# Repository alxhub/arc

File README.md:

# ARC — model railroad control

ARC is my hobby ecosystem of model railroad control systems. It is designed as an integrated, full stack system, from the computer running the layout to the boards powering track districts, moving turnouts, and lighting signal masts.

The design emphasizes global processing and specialized boards for dedicated tasks. A layout computer knows the track plan and coordinates the whole railroad, while distributed hardware provides the power, sensing, and local control each task needs. This gives the software a layout-wide view while keeping physical connections close to the equipment they serve.

ARC is designed for evolving and temporary layouts, with plug-and-play operation as a guiding goal. Common capabilities are available throughout the system, so changing the track plan can be an ordinary part of using the railroad. That flexibility goes hand in hand with intelligent control: the computer can use its knowledge of track connections and turnout positions to prepare the hardware for a route.

This repository contains ARC's schematics written in [Stackup](https://github.com/stackup-eda/stackup) and the corresponding KiCad PCB projects. Stackup is another of my projects: a declarative language and toolchain for describing electronic circuits as text. It expresses parts, reusable circuits, connections, and design constraints, checks them together, and exports the result for KiCad. Stackup uses KDL as its file syntax, which is why the schematic sources have a `.kdl` extension.

The architecture and intended system behavior are described below; individual board READMEs cover their roles and design decisions. [Control architecture](CONTROL.md) describes the administrative, operations, control, and field planes, including district policy and PSU authority on loss of communication. [ARC CAN protocol](PROTOCOL.md) defines the wire format and node identity scheme.

## Three levels of control

ARC organizes the layout into three levels:

1. **The layout computer**, usually a Raspberry Pi, knows the track plan, runs the layout, and coordinates its behavior. The ARC HAT connects the Pi to the backbone and provides control of the layout's master contactor.
2. **The ARC-Link backbone** connects primary functional boards, including DCC district drivers and Trackside Hubs, over CAN. These boards typically live together in one or more clusters around the layout and are DIN-rail mountable.
3. **Trackside bus legs** extend from those clusters along the rails. They connect boards that serve a local purpose, such as a signal mast, turnout, servo, or vehicle tag reader.

A **Trackside Hub is a backbone board** that connects these last two levels. It receives commands over ARC-Link and manages up to three separate trackside bus legs, using LIN for local signaling. This arrangement lets the backbone connect clusters of functional hardware while the trackside wiring follows the railroad to individual accessories.

## Power and installation

ARC is designed for industrial DC power supplies: **12 V for N scale** and **15 V for HO scale**, with a particular emphasis on DIN-rail mounted supplies. Primary backbone boards share that mounting approach, making it practical to assemble a cluster of power and control hardware together.

The power architecture distinguishes the supply carried by ARC-Link from the power delivered to the rails and accessories. The supply board switches power onto ARC-Link; district drivers and Trackside Hubs also have their own connections to the layout's supply for their loads. District drivers generate rail power locally from the shared DCC timing signal.

## ARC-Link: the backbone

ARC-Link carries power, CAN communication, and DCC synchronization over **eight-wire Ethernet cable**:

| Conductors | Purpose |
| --- | --- |
| 2 | Backbone power |
| 2 | Backbone ground |
| 2 | CAN differential pair for commands and status |
| 2 | DCC differential pair for synchronized track timing |

Ethernet cable is the wiring medium; ARC-Link uses CAN for communication. The separate DCC pair carries timing, not the traction current delivered to the rails. The supply board normally generates that timing, and district drivers use it to produce their individual DCC outputs.

**Ground loop isolation is a central design priority.** The supply board establishes the backbone's ground reference, and other active backbone boards isolate their local circuits from the link. This separates the backbone reference from local track supply returns and control wiring as the system extends between clusters around the layout.

ARC-Link is distinct from LCC. Support for LCC devices is planned through a dedicated **ARC ↔ LCC bridge**, allowing those devices to participate in the layout alongside ARC hardware.

## The trackside bus

The trackside bus uses **four-wire telephone cable with RJ-11 connectors**. Each leg carries four connections:

| Conductor | Purpose |
| --- | --- |
| Track voltage | The layout's track-voltage supply for local loads |
| 5 V | Low-voltage power |
| Ground | Local power and signaling return |
| LIN | Commands and status for trackside boards |

These legs typically parallel the rails, keeping accessory wiring near the devices it serves. A signal controller can sit near its mast, a turnout controller near its turnout machines, and a tag reader near its separate antenna flex.

Each Trackside Hub manages up to three legs and can switch them independently. Its backbone connection crosses an isolation boundary; the trackside legs share the hub's local power and return.

## A dedicated output for every district

ARC calls a track block a **district** and standardizes on a distinct, independently controlled power feed for each one. The system is optimized for many separate outputs, with district boards providing four, six, or eight outputs per board. This makes each district a unit of power control, sensing, and fault handling.

Every district is designed to include the same core capabilities:

- **Built-in block detection through drive-current sensing.** This detects locomotives, but does not detect resistive wheelsets.
- **Built-in autoreversing.** Each district can reverse its output phase as needed for reversing track arrangements, including advance changes coordinated by the layout computer.
- **Programming-track operation on demand.** Any district can serve as a fully featured programming track when needed, with a separate programming signal and a lower current limit.
- **Independent control and fault reporting.** Each output can be switched and monitored separately, so a fault can be identified and handled at the affected district.

These capabilities are part of the district design rather than separate accessories to add to selected sections. A district's role can change with the layout's needs, including switching between normal running and programming operation.

## Layouts that evolve, control that understands them

Having autoreversing available in every district makes it easier to experiment with the track plan. Add a reversing loop on a whim, and the surrounding districts already have the phase control they need: there is no need to carefully rewire them around a specially designated reversing output. Dedicated district feeds and a controller that knows the revised track plan provide the basis for this plug-and-play approach.

That global picture also enables proactive polarity control. ARC is designed to use the track plan and turnout configurations to align district polarities automatically before wheels cross a boundary and cause a short. The layout computer can coordinate the outputs involved in a route because it knows how those sections connect.

The Kato turntable controller is another example of this intended behavior. As the turntable spins, ARC can use its knowledge of the table's position and connecting tracks to align their polarities automatically. The specialized board operates the turntable, while the layout-wide picture makes coordinated track power possible.

## Backbone boards

| Board | Role |
| --- | --- |
| [ARC-PSU-01](backbone/psu-01/README.md) | Switches power onto ARC-Link and normally generates DCC timing. |
| [ARC-HAT-01](backbone/hat-01/README.md) | Connects a Raspberry Pi to CAN and controls the layout contactor. |
| [ARC-EX-ARC](backbone/ex-arc/README.md) | Connects a CommandStation-EX and its motor shield to ARC. |
| [ARC-TERM-01](backbone/term-01/README.md) | Terminates the CAN and DCC pairs at the end of a run. |
| [ARC-DST-01x4 rev 2](backbone/dst-01x4/README.md) | Drives four independent track districts. |
| [ARC-DST-01x6](backbone/dst-01x6/README.md) | Drives six independent track districts. |
| [ARC-DST-01x8](backbone/dst-01x8/README.md) | Drives eight independent track districts. |
| [ARC-YRD-01x8](backbone/yrd-01x8/README.md) | Controls yard turnouts and signal lamps. |
| [ARC-TRK-HUB-01](backbone/trk-hub-01/README.md) | Bridges backbone CAN to three trackside LIN runs. |

## Trackside boards

| Board | Role |
| --- | --- |
| [ARC-TRK-LED-01](trackside/trk-led-01/README.md) | Drives signal lamps on a LIN run. |
| [ARC-TRK-SRV-01](trackside/trk-srv-01/README.md) | Drives servos, sound, and a signal head. |
| [ARC-TRK-NFC-01](trackside/trk-nfc-01/README.md) | Reads vehicle tags with a separate antenna. |
| [ARC-TRK-ANT-01](trackside/trk-ant-01/README.md) | Provides the reader's flexible track antenna. |
| [ARC-TRK-TRN-01](trackside/trk-trn-01/README.md) | Operates four turnout machines. |
| [ARC-TRK-TBL-01xK](trackside/trk-tbl-01xK/README.md) | Operates a Kato turntable. |

## Firmware

The [Rust firmware workspace](firmware/README.md) uses Embassy. It contains the
shared ARC-Link protocol crate at `firmware/shared/link`, the shared DCC packet
and waveform generator at `firmware/shared/dcc`, the `dst-01` board
crate for x4 rev1/rev2, and the `psu-01` board crate for link power, a
bounded locomotive table, and DCC idle and speed packets. DST rev1 includes the
same transmitter, disabled at boot. PSU and DST rev1 both require
[CAN transmit permission](PROTOCOL.md#dcc-control-message-0x01-grant), retained until
the source restarts. Once the expected layout is good, layoutd selects one master
and grants permission. PSU link power and CAN discovery start independently of DCC.
All current firmware targets also use an Embassy bootloader and a shared
[CAN FD update protocol](PROTOCOL.md#firmware-update-over-can-fd) for staged
application updates.

## Layout software

The first host-side service is [layoutd](services/layoutd/README.md). It owns
retained MQTT facts about track nodes, derives and checks the layout graph
against observed CAN node identities, and publishes overall status. Its CAN interface supports file snapshots and the virtual CAN bus for development
and tests. It selects the DCC master only after all expected hardware is accounted for.

The initial [dispatchd](services/dispatchd/README.md) bridge reads district
status and PSU throttle status from the virtual CAN bus, publishes MQTT state
under `/<layout>/district/` and `/<layout>/loco/`, and converts non-retained
locomotive commands to CAN throttle-set frames. PSU and DST rev1 share the
locomotive table and require the transmit grant assigned by layoutd.

The [virtual CAN lab](sim/README.md) builds the DST-01x4 firmware crate as host
binaries for both board revisions and connects them over a simulated CAN bus.
Its world clock starts paused; tests advance it explicitly so CAN arbitration,
PSU and district timers, DCC delivery, track motion, and current sampling share
the same time. The physical track fixture is separate from layoutd's configured
layout, allowing tests to exercise unknown or incorrect track plans.

## Working with the designs

The boards are composed from reusable Stackup circuits in [`shared/`](shared/). Each board directory keeps its `board.kdl`, supporting Stackup sources, functional README, and KiCad PCB project together.

The designs import the [Stackup parts library](https://github.com/stackup-eda/library), pinned in `manifest.kdl`. For local development, add a `manifest.local.kdl` with a path to a parts checkout:

```kdl
library stackup path="../stackup-parts"
```

Run `stackup check backbone/psu-01/board.kdl` to validate a board. Substitute any other board's `board.kdl` path as needed. Use `--locked` to check against the pinned library commit. Without a local override, the CLI fetches Git libraries into `.stackup/cache/` beside `manifest.kdl`.

Each KiCad PCB has a `.stackup_sch` sidecar pointing to the adjacent `board.kdl`. To sync a closed board with the Stackup KiCad plugin, using KiCad's bundled Python (`STACKUP_KDL` is the path to the Stackup worktree):

```sh
/Applications/KiCad/KiCad.app/Contents/Frameworks/Python.framework/Versions/3.9/bin/python3 \
  "$STACKUP_KDL/kicad-plugin/sync_headless.py" \
  backbone/term-01/term-01.kicad_pcb
```

The PCB layouts retain their routed copper and KiCad project settings. Some newer parts in the district and yard schematics still need placement and routing. A Stackup check or PCB sync is not a DRC or fabrication signoff. The antenna board retains an older footprint table as `fp-lib-table.legacy` for reference; KiCad uses its existing `fp-lib-table`.

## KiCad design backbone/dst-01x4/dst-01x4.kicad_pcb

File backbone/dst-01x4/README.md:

# ARC-DST-01x4 rev 2

ARC-DST-01x4 drives four track districts. It receives the shared DCC timing signal from the ARC backbone, then lets the controller set each district's phase and turn each output on or off independently. A district can also switch to a separate programming signal with a lower current limit.

The board has its own connection to the layout's track supply. It reports total track current and supply voltage to the controller, while each district reports its own current and fault state. That lets the system identify and respond to a problem in one section without treating all four sections as one output.

CAN connects the board to the rest of ARC for commands and status. The backbone's electrical isolation keeps its return separate from the track supply return. Board and district lights show status locally; a temperature sensor and fan support operation under load.

[Board design](board.kdl)
[PCB layout](dst-01x4.kicad_pcb)

## Firmware revisions

The Embassy firmware crate is [`firmware/dst-01`](../../firmware/dst-01), with
the `x4` variant feature and exactly one hardware revision feature:

| Feature | MCU | District control |
| --- | --- | --- |
| `rev1` | STM32G0B1RE | Two TCA9534 I/O expanders at `0x20` and `0x21`, on I²C3 (PC0 SCL / PC1 SDA) |
| `rev2` | STM32C092CB | Direct MCU GPIO, as described in the adjacent KDL sources |

Rev1's expanders carry phase, programming selection, sleep, and fault signals;
its PWM gates and analog sense inputs connect directly to the MCU. Rev1 is still
a firmware build target even though its Stackup design toolchain is retired.
Its reference is `pre-kdl-local`: the preserved firmware pin map is
`firmware/dst-01x4/src/pins/mk1_rev1.rs`, and the hardware source immediately before
commit `b27db1e` describes rev1. The branch tip's hardware source already describes
rev2, so it must not be used as the rev1 pin map.

Rev1 also has a backbone DCC transmitter: TIM14 channel 1 on PC12 (AF2), with
PC13 controlling driver-enable. Firmware uses the shared `dcc` crate for idle and
128-step speed packets and the timer waveform, clocked from the board's 40 MHz
oscillator. TIM3 remains reserved for Embassy time. The transmitter initializes
disabled and accepts the same [CAN transmit grant](../../PROTOCOL.md#dcc-control-message-0x01-grant)
as PSU. Permission persists until MCU restart. The active-low link-good input
on PC2 gates actual transmission without clearing permission.
Generation alone does not mark the received source ready or enable districts.
Rev2 has no corresponding transmitter support.

Rev1 routes USB D−/D+ to PA11/PA12. Firmware presents a CDC debug console for
local DCC master and throttle commands, district state transitions, nominal
current logging, reboot to the STM32 ROM USB DFU bootloader, and an `erase`
command that clears the first flash page for bootloader replacement. See the
[console command reference](../../firmware/README.md#rev1-usb-debug-console).

Rev1's small green D4 uses `logic/brick/+`. Its RGB D3 uses the separate
`indicator/lamp_rail/+`, supplied by U25 from `VPWR` and connected to D3 pad 4.
During bring-up, board #1 ran the LED task and blinked D4 but did not light D3;
D3 pad 4 measured about 4.5 V, so the lamp rail is reaching D3. The remaining
checks are the PC7/PD9/PD8 sinks through R39/R40/R41 and D3's solder joints or
orientation. On board #1, grounding the RGB resistor paths with a meter lit
red and blue but not green. This suggests the red and blue dies and their common
anode can conduct, while their normal GPIO sink path still needs checking;
green may have a separate resistor, joint, or die fault.

See [firmware build instructions](../../firmware/README.md).

## District tasks and recovery

Firmware starts one Embassy task per district. Each owns its active configuration,
hardware handle, and recovery state. `Disabled`, `Synced`, and `Programming` select
whether the district is off or takes the backbone or programming stream. All
districts boot disabled. A separate source-readiness interlock must also allow the
selected stream; the DCC receiver and programming generator have not yet been
implemented, so both readiness flags currently stay false and the rails stay off.

The task uses a `DistrictHal` abstraction. Rev1 serializes access to its two
expanders, preserving the other district's output bits; rev2 uses direct GPIO.
The implementations handle the opposite programming-select polarities (rev1
active high, rev2 active low). Both read ADC current sense and active-low fault
signals, and both can inhibit the district through a direct MCU gate without
waiting for I²C. Source/range changes happen with the gate off. Phase is held
normal; autoreversing is not implemented yet.

Short recovery limits average delivered energy with **burst duty limiting**:
short powered probes separated by unpowered intervals, rather than high-frequency
PWM over the DCC signal. The initial policy is:

- A probe is nominally 2 ms on, followed by at least 40 ms off (about 4.8% duty).
- A bad powered sample immediately ends the probe or continuous drive. The off
  interval doubles after each failed probe, up to 10 seconds.
- Ten consecutive clear probes restore continuous drive. Readings taken while
  off never count as clearance. Startup also passes through these probes.
- Five seconds of healthy continuous operation resets the backoff. Configuration
  changes and disabling/re-enabling cannot erase accumulated short backoff.
- Hardware I/O errors latch that district off. An explicit disabled configuration
  clears the latch; a subsequent enabled configuration starts recovery again.

These timings are local firmware policy, with nominal retry duty at or below
10%. The backoff follows the approach in CommandStation-EX's
`MotorDriver::checkPowerOverload`; its fault-ignore delays and brake PWM are not
ported. The first millisecond of each probe allows driver wake-up and sense-filter
settling. Software trips at 90% of the nominal analog trip-reference voltage:
ADC counts 3334 on rev1 and 2780 on rev2, for either current range. These are
initial engineering thresholds, not calibrated current measurements.

The tasks poll at approximately 1 ms intervals. Shared-bus transactions and
scheduling add latency, so probe durations and duty ratios are nominal, not
hardware-enforced bounds. The DRV8874's local current limiting remains necessary.
Bench validation of thresholds, wake-up timing, short energy, and recovery with
real loads is still required. TIM3 currently supplies Embassy time and must be
reassigned before using it for rev2's pixel stream. The [district configuration
CAN message](../../PROTOCOL.md#district-control-message-0x01-configuration) and
periodic and state-change [status message](../../PROTOCOL.md#district-status-message-0x01-status)
are wired to FDCAN1 on both revisions and exercised in the virtual CAN lab.
Hardware CAN validation, calibrated current measurement,
DCC source readiness, programming generation, and autoreversing remain pending.

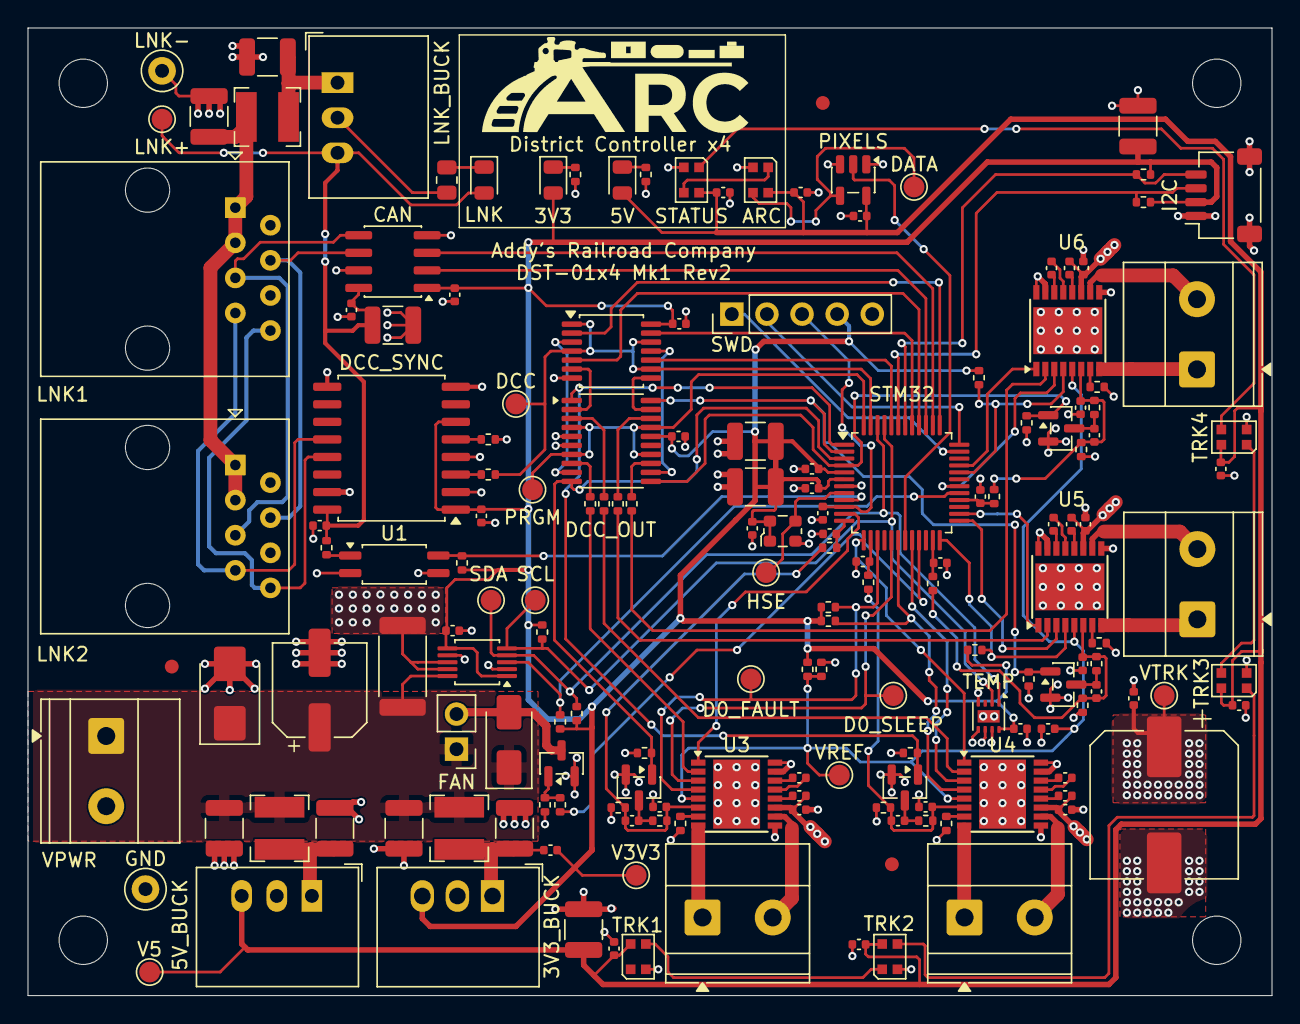
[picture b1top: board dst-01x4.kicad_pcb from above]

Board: 4 copper layers, 90.0 x 70.0 mm, 172 parts (0 on the bottom side), 114 nets.

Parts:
3V3, 5V: green; LED_0805_2012Metric
3V3_BUCK: R-78K3.3-0.5; Converter_DCDC_RECOM_R-78K-0.5_THT
5V_BUCK: R-78E5.0-0.5; Converter_DCDC_RECOM_R-78E-0.5_THT
ARC: WS2812B-2020; LED_WS2812B-2020_PLCC4_2.0x2.0mm
C1: 47µF; CP_Elec_6.3x7.7
C2, C3, C8, C17, C19, C32: 10µF; C_1210_3225Metric
C4, C56, C57, C58, C59: 1nF; C_0402_1005Metric
C5, C7, C10, C11, C12, C13, C14, C15, C16, C18, C21, C22, C24, C25, C26, C28, C30, C31, C33, C34, C35, C36, C38, C40, C41, C43, C45, C46, C48, C50, C51, C53, C55: 100nF; C_0402_1005Metric
C6: 220µF; CP_Elec_10x16.5
C9, C20, C23, C27: 4.7µF; C_1210_3225Metric
C29: 1µF; C_1210_3225Metric
C37, C42, C47, C52: 22nF; C_0402_1005Metric
C39, C44, C49, C54: 10nF; C_0402_1005Metric
CAN: ISO1044BD; SOIC-8_3.9x4.9mm_P1.27mm
D0_FAULT, D0_SLEEP: TestPoint; TestPoint_Pad_D1.5mm
D1: SMBJ18A; D_SMB
D2, D3, D4, D5: WS2812B-2020; LED_WS2812B-2020_PLCC4_2.0x2.0mm
D6: SS14; D_SMA
DATA: TestPoint; TestPoint_Pad_D1.5mm
DCC: TestPoint; TestPoint_Pad_D1.5mm
DCC_OUT: ADG734; TSSOP-20_4.4x6.5mm_P0.65mm
DCC_SYNC: ISO1430DW; SOIC-16W_7.5x10.3mm_P1.27mm
FAN: Conn_01x02; PinHeader_1x02_P2.54mm_Vertical
FID1, FID2, FID3: Fiducial; Fiducial_1mm_Mask2mm
GND: TestPoint; TestPoint_Loop_D2.50mm_Drill1.0mm
H1, H2, H3, H4: MountingHole; MountingHole_3.5mm
HSE: TestPoint; TestPoint_Pad_D1.5mm
I2C: Conn_01x04_MountingPin; JST_SH_SM04B-SRSS-TB_1x04-1MP_P1.00mm_Horizontal
L1: 100µH; L_Bourns-SRN4018
L2, L3: 15µH; L_Bourns-SRN4018
LNK: green; LED_0805_2012Metric
LNK1, LNK2: RJ45; RJ45_Amphenol_54602-x08_Horizontal
LNK+: TestPoint; TestPoint_Pad_D1.5mm
LNK-: TestPoint; TestPoint_Loop_D2.50mm_Drill1.0mm
LNK_BUCK: R-78E5.0-0.5; Converter_DCDC_RECOM_R-78E-0.5_THT
MON: INA226; TSSOP-10_3x3mm_P0.5mm
PIXELS: 74AHCT1G125; SOT-23-5
PRGM: TestPoint; TestPoint_Pad_D1.5mm
Q1: DMN3404L; SOT-23
Q2, Q3, Q4, Q5: BSS138; SOT-23
R1: 5mΩ; R_2512_6332Metric
R2, R42, R43, R44, R45: 1kΩ; R_0402_1005Metric
R3: 100Ω; R_0402_1005Metric
R4, R6, R18, R23, R28, R33: 10kΩ; R_0402_1005Metric
R5: 300Ω; R_0805_2012Metric
R7: 2kΩ; R_0402_1005Metric
R8, R20, R25, R30, R35: 100kΩ; R_0402_1005Metric
R9: 680Ω; R_0402_1005Metric
R10: 1.5kΩ; R_0402_1005Metric
R11, R12, R13, R14: 4.7kΩ; R_0402_1005Metric
R15: 33Ω; R_0402_1005Metric
R16: 9.76kΩ; R_0402_1005Metric
R17: 30kΩ; R_0402_1005Metric
R19, R24, R29, R34: 20kΩ; R_0402_1005Metric
R21, R26, R31, R36: 22.1kΩ; R_0402_1005Metric
R22, R27, R32, R37: 2.49kΩ; R_0402_1005Metric
R38, R39, R40, R41: 22Ω; R_0402_1005Metric
SCL: TestPoint; TestPoint_Pad_D1.5mm
SDA: TestPoint; TestPoint_Pad_D1.5mm
STATUS: WS2812B-2020; LED_WS2812B-2020_PLCC4_2.0x2.0mm
STM32: STM32C092CBTx; LQFP-48_7x7mm_P0.5mm
SWD: Conn_01x05; PinHeader_1x05_P2.54mm_Vertical
TEMP: TMP1075DSG; WSON-8-1EP_2x2mm_P0.5mm_EP0.9x1.6mm
TRK1, TRK2, TRK3, TRK4: Conn_01x02; TerminalBlock_Phoenix_MKDS-1,5-2-5.08_1x02_P5.08mm_Horizont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
U1: FODM217A; SOP-4_4.4x2.6mm_P1.27mm
U2: 74HC86; TSSOP-14_4.4x5mm_P0.65mm
U3, U4, U5, U6: DRV8874PWPR; HTSSOP-16-1EP_4.4x5mm_P0.65mm_EP3.4x5mm
V3V3, V5: TestPoint; TestPoint_Pad_D1.5mm
VPWR: Conn_01x02; TerminalBlock_Phoenix_MKDS-1,5-2-5.08_1x02_P5.08mm_Horizont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
VREF: TestPoint; TestPoint_Pad_D1.5mm
VTRK: TestPoint; TestPoint_Pad_D1.5mm
Y1: 40MHz; Oscillator_SMD_ECS_2520MV-xxx-xx-4Pin_2.5x2.0mm

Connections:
DCC: DCC.1, R15.2, STM32.47, U2.1, U2.4, U2.9, U2.12
DCC_PROG: DCC_OUT.4, DCC_OUT.7, DCC_OUT.14, DCC_OUT.17, PRGM.1, STM32.48
DCC_RO: DCC_SYNC.3, R15.1
unnamed: 3V3.1, R9.1
unnamed: 3V3_BUCK.1, C3.1, C4.1, L1.2
unnamed: 5V.1, R10.1
unnamed: 5V_BUCK.1, C9.1, L2.2
unnamed: ARC.1, STATUS.3
unnamed: D2.1, D3.3
unnamed: D3.1, D4.3
unnamed: D4.1, D5.3
unnamed: LNK.1, R5.1
unnamed: C20.1, L3.2, LNK_BUCK.1
unnamed: Q1.1, R3.2, R4.1
unnamed: C40.2, Q2.3, R22.2
unnamed: C45.2, Q3.3, R27.2
unnamed: C50.2, Q4.3, R32.2
unnamed: C55.2, Q5.3, R37.2
unnamed: R7.2, U1.1
unnamed: C37.1, U3.13
unnamed: C37.2, U3.14
unnamed: R19.1, U3.7
unnamed: C38.2, U3.12
unnamed: C42.1, U4.13
unnamed: C42.2, U4.14
unnamed: R24.1, U4.7
unnamed: C43.2, U4.12
unnamed: C47.1, U5.13
unnamed: C47.2, U5.14
unnamed: R29.1, U5.7
unnamed: C48.2, U5.12
unnamed: C52.1, U6.13
unnamed: C52.2, U6.14
unnamed: R34.1, U6.7
unnamed: C53.2, U6.12
PHASE0: STM32.37, U2.2
PHASE1: STM32.40, U2.5
PHASE2: STM32.44, U2.10
PHASE3: STM32.41, U2.13
SIGNAL0: DCC_OUT.8, R38.1
SIGNAL1: DCC_OUT.3, R39.1
SIGNAL2: DCC_OUT.18, R40.1
SIGNAL3: DCC_OUT.13, R41.1
STREAM0: DCC_OUT.9, U2.3
STREAM1: DCC_OUT.2, U2.6
STREAM2: DCC_OUT.19, U2.8
STREAM3: DCC_OUT.12, U2.11
VREF: C35.1, R16.2, R17.1, U3.5, U4.5, U5.5, U6.5, VREF.1
adc0/adc: C56.1, R42.1, STM32.12
adc1/adc: C57.1, R43.1, STM32.14
adc2/adc: C58.1, R44.1, STM32.23
adc3/adc: C59.1, R45.1, STM32.28
d0/A: TRK1.1, U3.8
d0/B: TRK1.2, U3.10
d0/DCC: R38.2, U3.2
d0/ISENSE: C39.1, C40.1, R21.1, R22.1, R42.2, U3.6
d0/PWM: STM32.11, U3.1
d0/nFAULT: D0_FAULT.1, R18.1, STM32.15, U3.4
d0/nSLEEP: D0_SLEEP.1, STM32.17, U3.3
d1/A: TRK2.1, U4.8
d1/B: TRK2.2, U4.10
d1/DCC: R39.2, U4.2
d1/ISENSE: C44.1, C45.1, R26.1, R27.1, R43.2, U4.6
d1/PWM: STM32.13, U4.1
d1/nFAULT: R23.1, STM32.18, U4.4
d1/nSLEEP: STM32.20, U4.3
d2/A: TRK3.1, U5.8
d2/B: TRK3.2, U5.10
d2/DCC: R40.2, U5.2
d2/ISENSE: C49.1, C50.1, R31.1, R32.1, R44.2, U5.6
d2/PWM: STM32.26, U5.1
d2/nFAULT: R28.1, STM32.24, U5.4
d2/nSLEEP: STM32.25, U5.3
d3/A: TRK4.1, U6.8
d3/B: TRK4.2, U6.10
d3/DCC: R41.2, U6.2
d3/ISENSE: C54.1, C55.1, R36.1, R37.1, R45.2, U6.6
d3/PWM: STM32.33, U6.1
d3/nFAULT: R33.1, STM32.32, U6.4
d3/nSLEEP: STM32.30, U6.3
dc/GND: 3V3_BUCK.2, 5V_BUCK.2, ARC.2, C1.2, C2.2, C3.2, C5.2, C6.2, C7.2, C8.2, C9.2, C10.2, C11.2, C12.2, C13.2, C14.2, C15.2, C16.2, C17.2, C18.2, C21.2, C24.2, C26.2, C27.2, C28.2, C29.2, C30.2, C31.2, C32.2, C33.2, C34.2, C35.2, C36.2, C39.2, C41.2, C44.2, C46.2, C49.2, C51.2, C54.2, C56.2, C57.2, C58.2, C59.2, CAN.4, D1.2, D2.2, D3.2, D4.2, D5.2, DCC_OUT.5, DCC_OUT.6, DCC_SYNC.2, DCC_SYNC.4, DCC_SYNC.8, GND.1, I2C.1, I2C.MP, MON.2, MON.7, PIXELS.1, PIXELS.3, Q1.2, Q2.2, Q3.2, Q4.2, Q5.2, R4.2, R6.2, R9.2, R10.2, R17.2, R19.2, R20.2, R21.2, R24.2, R25.2, R26.2, R29.2, R30.2, R31.2, R34.2, R35.2, R36.2, STATUS.2, STM32.7, SWD.5, TEMP.4, TEMP.5, TEMP.6, TEMP.7, TEMP.9, U1.3, U2.7, U3.9, U3.15, U3.16, U3.17, U4.9, U4.15, U4.16, U4.17, U5.9, U5.15, U5.16, U5.17, U6.9, U6.15, U6.16, U6.17, VPWR.2, Y1.2
dc/VPWR: C1.1, C2.1, C8.1, D1.1, D6.1, FAN.1, L1.1, L2.1, MON.10, R1.1, VPWR.1
exp-pulls/i2c.scl: I2C.4, R14.1, STM32.42
exp-pulls/i2c.sda: I2C.3, R13.1, STM32.43
fan/en: R3.1, STM32.21
hse: HSE.1, STM32.8, Y1.3
indicator/DIN: ARC.3, DATA.1, PIXELS.4
indicator/board/out: D2.3, STATUS.1
indicator/data: PIXELS.2, STM32.19
indicator/v5.rail: 5V.2, 5V_BUCK.3, ARC.4, C10.1, C11.1, C12.1, C13.1, C14.1, C15.1, C16.1, C17.1, D2.4, D3.4, D4.4, D5.4, PIXELS.5, STATUS.4, V5.1
link/V5_LINK: C22.1, C23.1, C25.1, CAN.8, DCC_SYNC.16, LNK.2, LNK+.1, LNK_BUCK.3, R7.1
link/VLINK: C19.1, L3.1, LNK1.1, LNK1.3, LNK2.1, LNK2.3
link/VLINK_GND: C19.2, C20.2, C22.2, C23.2, C25.2, CAN.7, DCC_SYNC.9, DCC_SYNC.15, LNK1.2, LNK1.6, LNK2.2, LNK2.6, LNK-.1, LNK_BUCK.2, R5.2, U1.2
link/dcc-de: DCC_SYNC.5, R6.1
link/fdcan.rx: CAN.3, STM32.38
link/fdcan.tx: CAN.2, STM32.39
link/good: R8.1, STM32.9, U1.4
link/jacks/CANH: CAN.6, LNK1.4, LNK2.4
link/jacks/CANL: CAN.5, LNK1.5, LNK2.5
link/jacks/DCC_A: DCC_SYNC.12, LNK1.7, LNK2.7
link/jacks/DCC_B: DCC_SYNC.13, LNK1.8, LNK2.8
nALERT: MON.3, R2.1, STM32.29
nPROG0: DCC_OUT.10, Q2.1, R20.1, STM32.3
nPROG1: DCC_OUT.1, Q3.1, R25.1, STM32.1
nPROG2: DCC_OUT.20, Q4.1, R30.1, STM32.2
nPROG3: DCC_OUT.11, Q5.1, R35.1, STM32.4
nrst: C28.1, STM32.10, SWD.3
swd/swd.swclk: STM32.36, SWD.2
swd/swd.swdio: STM32.35, SWD.1
thermal/fan/-: D6.2, FAN.2, Q1.3
track/VTRK: C6.1, C7.1, C36.1, C38.1, C41.1, C43.1, C46.1, C48.1, C51.1, C53.1, MON.8, MON.9, R1.2, U3.11, U4.11, U5.11, U6.11, VTRK.1
track/i2c.scl: MON.5, R12.1, SCL.1, STM32.45, TEMP.2
track/i2c.sda: MON.4, R11.1, SDA.1, STM32.46, TEMP.1
track/logic.rail: 3V3.2, 3V3_BUCK.3, C4.2, C5.1, C18.1, C21.1, C24.1, C26.1, C27.1, C29.1, C30.1, C31.1, C32.1, C33.1, C34.1, CAN.1, DCC_OUT.16, DCC_SYNC.1, DCC_SYNC.6, I2C.2, MON.1, MON.6, R2.2, R8.2, R11.2, R12.2, R13.2, R14.2, R16.1, R18.2, R23.2, R28.2, R33.2, STM32.5, STM32.6, SWD.4, TEMP.8, U2.14, V3V3.1, Y1.1, Y1.4

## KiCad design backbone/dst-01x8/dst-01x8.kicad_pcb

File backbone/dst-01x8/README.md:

# ARC-DST-01x8

ARC-DST-01x8 drives eight independent track districts from the layout's track supply. It receives the shared DCC timing signal over the ARC backbone and uses CAN for commands and status.

Each district can switch between running trains and a lower current programming mode. The controller receives a separate fault and current measurement from every district, plus a measurement of total track current. Two temperature sensors watch the board's two groups of four districts.

This board lets a larger area of a layout share one controller and backbone connection while keeping its track outputs independent. Its backbone connection is electrically isolated from the track supply, and its DC input protects against a reversed field connection.

[Board design](board.kdl)
[PCB layout](dst-01x8.kicad_pcb)

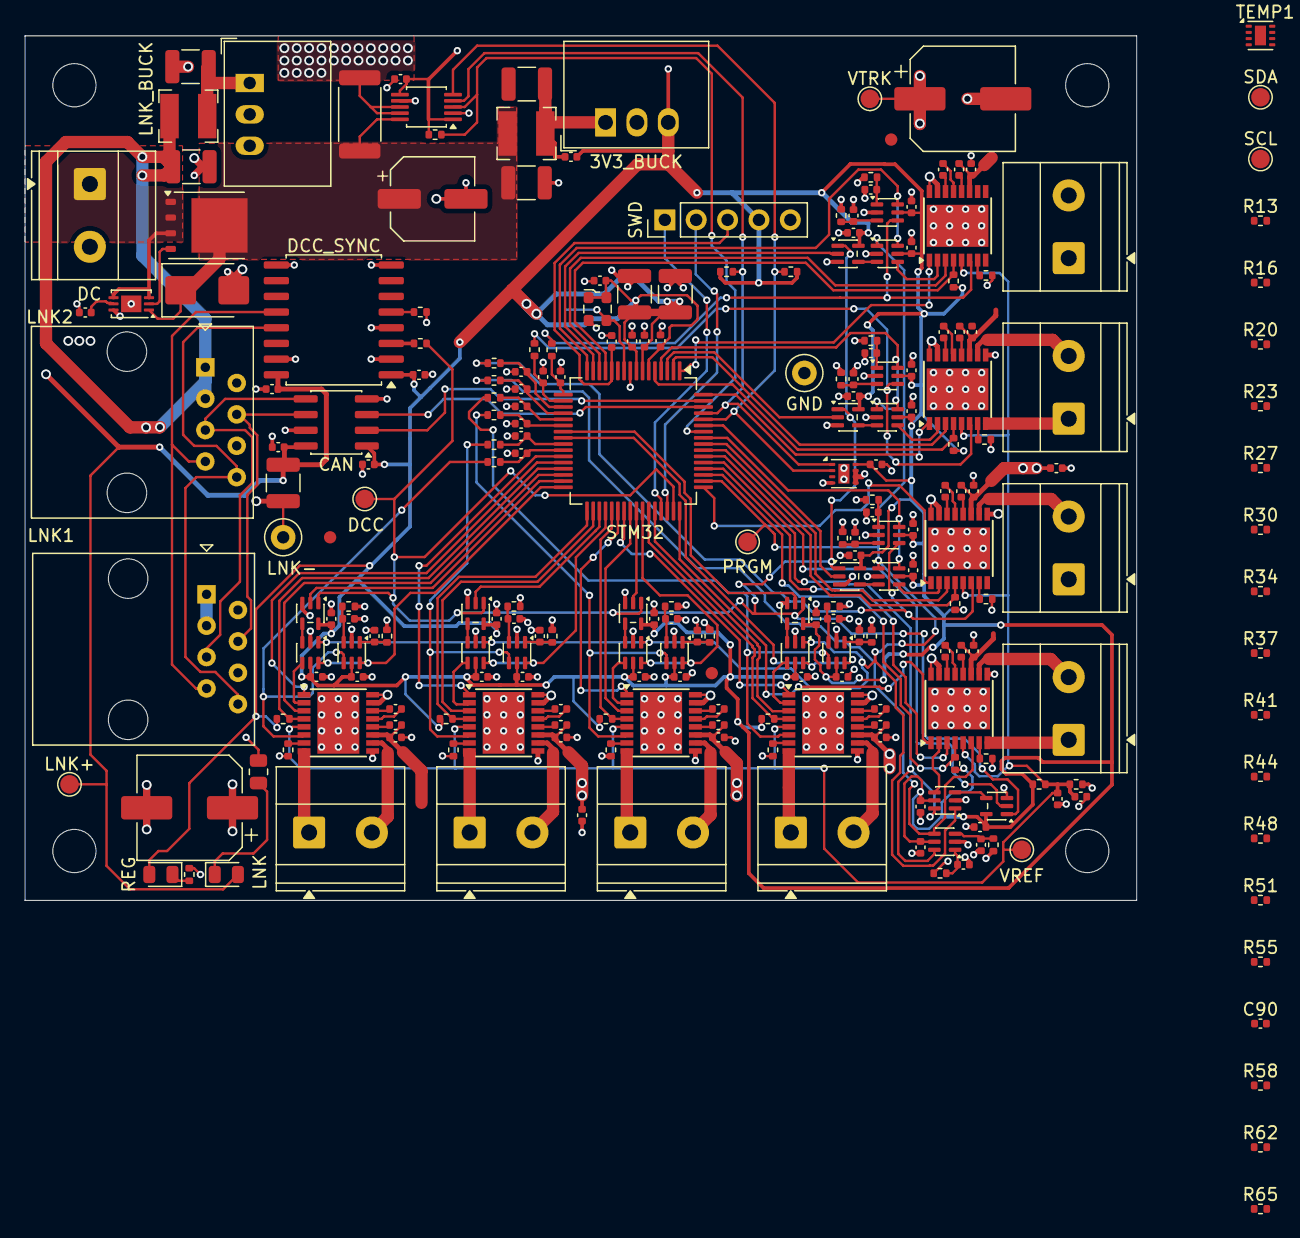
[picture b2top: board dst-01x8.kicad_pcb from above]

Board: 4 copper layers, 90.0 x 70.0 mm, 243 parts (1 on the bottom side), 176 nets.

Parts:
3V3_BUCK: R-78K3.3-0.5; Converter_DCDC_RECOM_R-78K-0.5_THT
C1, C34, C43, C52, C61, C70, C79, C88, C97: 10nF; C_0402_1005Metric
C2: 47µF; CP_Elec_6.3x7.7
C3, C4, C15: 10µF; C_1210_3225Metric
C5, C37, C46, C55, C64, C73, C82, C91, C100: 1nF; C_0402_1005Metric
C6, C9, C10, C11, C12, C13, C14, C17, C18, C20, C21, C22, C24, C25, C27, C28, C29, C31, C32, C33, C35, C36, C38, C40, C41, C42, C44, C45, C47, C49, C50, C51, C53, C54, C56, C58, C59, C60, C62, C63, C65, C67, C68, C69, C71, C72, C74, C76, C77, C78, C80, C81, C83, C85, C86, C87, C89, C90, C92, C94, C95, C96, C98, C99: 100nF; C_0402_1005Metric
C7, C8: 100µF; CP_Elec_8x11.9
C16, C19, C23: 4.7µF; C_1210_3225Metric
C26: 1µF; C_1210_3225Metric
C30, C39, C48, C57, C66, C75, C84, C93: 22nF; C_0402_1005Metric
CAN: ISO1044BD; SOIC-8_3.9x4.9mm_P1.27mm
D1: SMBJ18A; D_SMB
DC: Conn_01x02; TerminalBlock_Phoenix_MKDS-1,5-2-5.08_1x02_P5.08mm_Horizont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
DCC: TestPoint; TestPoint_Pad_D1.5mm
DCC_SYNC: ISO1430DW; SOIC-16W_7.5x10.3mm_P1.27mm
FID1, FID2, FID3: Fiducial; Fiducial_1mm_Mask2mm
GND: TestPoint; TestPoint_Loop_D2.50mm_Drill1.0mm
H1, H2, H3, H4: MountingHole; MountingHole_3.5mm
HSE: TestPoint; TestPoint_Pad_D1.5mm
L1: 100µH; L_Bourns-SRN4018
L2: 15µH; L_Bourns-SRN4018
LNK: green; LED_0805_2012Metric
LNK1, LNK2: RJ45; RJ45_Amphenol_54602-x08_Horizontal
LNK+: TestPoint; TestPoint_Pad_D1.5mm
LNK-: TestPoint; TestPoint_Loop_D2.50mm_Drill1.0mm
LNK_BUCK: R-78E5.0-0.5; Converter_DCDC_RECOM_R-78E-0.5_THT
MON: INA226; TSSOP-10_3x3mm_P0.5mm
PRGM: TestPoint; TestPoint_Pad_D1.5mm
Q1: BSC030N08NS5; TDSON-8-1
R1: 3mΩ; R_2512_6332Metric
R2, R17, R24, R31, R38, R45, R52, R59, R66: 1kΩ; R_0402_1005Metric
R3: 9.76kΩ; R_0402_1005Metric
R4: 30kΩ; R_0402_1005Metric
R5: 300Ω; R_0805_2012Metric
R6, R11, R18, R25, R32, R39, R46, R53, R60: 10kΩ; R_0402_1005Metric
R7: 680Ω; R_0402_1005Metric
R8, R9: 4.7kΩ; R_0402_1005Metric
R10: 33Ω; R_0402_1005Metric
R12, R19, R26, R33, R40, R47, R54, R61: 20kΩ; R_0402_1005Metric
R13, R20, R27, R34, R41, R48, R55, R62: 100kΩ; R_0402_1005Metric
R14, R21, R28, R35, R42, R49, R56, R63: 2.21kΩ; R_0402_1005Metric
R15, R22, R29, R36, R43, R50, R57, R64: 22.1kΩ; R_0402_1005Metric
R16, R23, R30, R37, R44, R51, R58, R65: 22Ω; R_0402_1005Metric
REG: green; LED_0805_2012Metric
SCL: TestPoint; TestPoint_Pad_D1.5mm
SDA: TestPoint; TestPoint_Pad_D1.5mm
STM32: STM32G0B1RETx; LQFP-64_10x10mm_P0.5mm
SWD: Conn_01x05; PinHeader_1x05_P2.54mm_Vertical
TEMP0, TEMP1: TMP1075DSG; WSON-8-1EP_2x2mm_P0.5mm_EP0.9x1.6mm
TRK1, TRK2, TRK3, TRK4, TRK5, TRK6, TRK7, TRK8: Conn_01x02; TerminalBlock_Phoenix_MKDS-1,5-2-5.08_1x02_P5.08mm_Horizont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
U1: LTC4359-DCB; DFN-6-1EP_3x2mm_P0.5mm_EP1.65x1.35mm
U2, U6, U10, U14, U18, U22, U26, U30: DRV8874PWPR; HTSSOP-16-1EP_4.4x5mm_P0.65mm_EP3.4x5mm
U3, U5, U7, U9, U11, U13, U15, U17, U19, U21, U23, U25, U27, U29, U31, U33: 74LVC1G3157; SOT-363_SC-70-6
U4, U8, U12, U16, U20, U24, U28, U32: 74LVC1G86; SOT-353_SC-70-5
VREF: TestPoint; TestPoint_Pad_D1.5mm
VTRK: TestPoint; TestPoint_Pad_D1.5mm
Y1: 40MHz; Oscillator_SMD_ECS_2520MV-xxx-xx-4Pin_2.5x2.0mm

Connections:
DCC: DCC.1, R10.2, STM32.47, U4.1, U8.1, U12.1, U16.1, U20.1, U24.1, U28.1, U32.1
DCC_PROG: PRGM.1, STM32.50, U5.1, U9.1, U13.1, U17.1, U21.1, U25.1, U29.1, U33.1
DCC_RO: DCC_SYNC.3, R10.1
unnamed: 3V3_BUCK.1, C4.1, C5.1, L1.2
unnamed: LNK.1, R5.1
unnamed: C16.1, L2.2, LNK_BUCK.1
unnamed: R7.1, REG.1
unnamed: Q1.4, U1.2
unnamed: C1.1, U1.5
unnamed: C30.1, U2.13
unnamed: C30.2, U2.14
unnamed: R12.1, U2.7
unnamed: C31.2, U2.12
unnamed: C33.1, R14.1, U3.3
unnamed: C34.1, R15.1, U3.1
unnamed: C39.1, U6.13
unnamed: C39.2, U6.14
unnamed: R19.1, U6.7
unnamed: C40.2, U6.12
unnamed: C42.1, R21.1, U7.3
unnamed: C43.1, R22.1, U7.1
unnamed: C48.1, U10.13
unnamed: C48.2, U10.14
unnamed: R26.1, U10.7
unnamed: C49.2, U10.12
unnamed: C51.1, R28.1, U11.3
unnamed: C52.1, R29.1, U11.1
unnamed: C57.1, U14.13
unnamed: C57.2, U14.14
unnamed: R33.1, U14.7
unnamed: C58.2, U14.12
unnamed: C60.1, R35.1, U15.3
unnamed: C61.1, R36.1, U15.1
unnamed: C66.1, U18.13
unnamed: C66.2, U18.14
unnamed: R40.1, U18.7
unnamed: C67.2, U18.12
unnamed: C69.1, R42.1, U19.3
unnamed: C70.1, R43.1, U19.1
unnamed: C75.1, U22.13
unnamed: C75.2, U22.14
unnamed: R47.1, U22.7
unnamed: C76.2, U22.12
unnamed: C78.1, R49.1, U23.3
unnamed: C79.1, R50.1, U23.1
unnamed: C84.1, U26.13
unnamed: C84.2, U26.14
unnamed: R54.1, U26.7
unnamed: C85.2, U26.12
unnamed: C87.1, R56.1, U27.3
unnamed: C88.1, R57.1, U27.1
unnamed: C93.1, U30.13
unnamed: C93.2, U30.14
unnamed: R61.1, U30.7
unnamed: C94.2, U30.12
unnamed: C96.1, R63.1, U31.3
unnamed: C97.1, R64.1, U31.1
PHASE0: STM32.31, U4.2
PHASE1: STM32.35, U8.2
PHASE2: STM32.41, U12.2
PHASE3: STM32.23, U16.2
PHASE4: STM32.54, U20.2
PHASE5: STM32.57, U24.2
PHASE6: STM32.3, U28.2
PHASE7: STM32.15, U32.2
PROG0: STM32.32, U3.6, U5.6
PROG1: STM32.36, U7.6, U9.6
PROG2: STM32.42, U11.6, U13.6
PROG3: STM32.24, U15.6, U17.6
PROG4: STM32.53, U19.6, U21.6
PROG5: STM32.59, U23.6, U25.6
PROG6: STM32.4, U27.6, U29.6
PROG7: STM32.16, U31.6, U33.6
SIGNAL0: R16.1, U5.4
SIGNAL1: R23.1, U9.4
SIGNAL2: R30.1, U13.4
SIGNAL3: R37.1, U17.4
SIGNAL4: R44.1, U21.4
SIGNAL5: R51.1, U25.4
SIGNAL6: R58.1, U29.4
SIGNAL7: R65.1, U33.4
STREAM0: U4.4, U5.3
STREAM1: U8.4, U9.3
STREAM2: U12.4, U13.3
STREAM3: U16.4, U17.3
STREAM4: U20.4, U21.3
STREAM5: U24.4, U25.3
STREAM6: U28.4, U29.3
STREAM7: U32.4, U33.3
adc0/adc: C37.1, R17.1, STM32.26
adc1/adc: C46.1, R24.1, STM32.25
adc2/adc: C55.1, R31.1, STM32.22
adc3/adc: C64.1, R38.1, STM32.21
adc4/adc: C73.1, R45.1, STM32.20
adc5/adc: C82.1, R52.1, STM32.19
adc6/adc: C91.1, R59.1, STM32.18
adc7/adc: C100.1, R66.1, STM32.17
d0/A: TRK1.1, U2.8
d0/B: TRK1.2, U2.10
d0/DCC: R16.2, U2.2
d0/ISENSE: R17.2, U2.6, U3.4
d0/PWM: STM32.28, U2.1
d0/nFAULT: R11.1, STM32.29, U2.4
d0/nSLEEP: R13.1, STM32.30, U2.3
d1/A: TRK2.1, U6.8
d1/B: TRK2.2, U6.10
d1/DCC: R23.2, U6.2
d1/ISENSE: R24.2, U6.6, U7.4
d1/PWM: STM32.27, U6.1
d1/nFAULT: R18.1, STM32.33, U6.4
d1/nSLEEP: R20.1, STM32.34, U6.3
d2/A: TRK3.1, U10.8
d2/B: TRK3.2, U10.10
d2/DCC: R30.2, U10.2
d2/ISENSE: R31.2, U10.6, U11.4
d2/PWM: STM32.38, U10.1
d2/nFAULT: R25.1, STM32.37, U10.4
d2/nSLEEP: R27.1, STM32.40, U10.3
d3/A: TRK4.1, U14.8
d3/B: TRK4.2, U14.10
d3/DCC: R37.2, U14.2
d3/ISENSE: R38.2, U14.6, U15.4
d3/PWM: STM32.39, U14.1
d3/nFAULT: R32.1, STM32.43, U14.4
d3/nSLEEP: R34.1, STM32.44, U14.3
d4/A: TRK5.1, U18.8
d4/B: TRK5.2, U18.10
d4/DCC: R44.2, U18.2
d4/ISENSE: R45.2, U18.6, U19.4
d4/PWM: STM32.48, U18.1
d4/nFAULT: R39.1, STM32.51, U18.4
d4/nSLEEP: R41.1, STM32.52, U18.3
d5/A: TRK6.1, U22.8
d5/B: TRK6.2, U22.10
d5/DCC: R51.2, U22.2
d5/ISENSE: R52.2, U22.6, U23.4
d5/PWM: STM32.49, U22.1
d5/nFAULT: R46.1, STM32.55, U22.4
d5/nSLEEP: R48.1, STM32.56, U22.3
d6/A: TRK7.1, U26.8
d6/B: TRK7.2, U26.10
d6/DCC: R58.2, U26.2
d6/ISENSE: R59.2, U26.6, U27.4
d6/PWM: STM32.64, U26.1
d6/nFAULT: R53.1, STM32.5, U26.4
d6/nSLEEP: R55.1, STM32.2, U26.3
d7/A: TRK8.1, U30.8
d7/B: TRK8.2, U30.10
d7/DCC: R65.2, U30.2
d7/ISENSE: R66.2, U30.6, U31.4
d7/PWM: STM32.1, U30.1
d7/nFAULT: R60.1, STM32.13, U30.4
d7/nSLEEP: R62.1, STM32.14, U30.3
dc/DC_IN: DC.1, Q1.1, Q1.2, Q1.3, U1.3, U1.4
dc/GND: 3V3_BUCK.2, C1.2, C2.2, C3.2, C4.2, C6.2, C7.2, C8.2, C9.2, C10.2, C11.2, C12.2, C13.2, C14.2, C17.2, C20.2, C22.2, C23.2, C24.2, C25.2, C26.2, C27.2, C28.2, C29.2, C32.2, C33.2, C34.2, C35.2, C36.2, C37.2, C38.2, C41.2, C42.2, C43.2, C44.2, C45.2, C46.2, C47.2, C50.2, C51.2, C52.2, C53.2, C54.2, C55.2, C56.2, C59.2, C60.2, C61.2, C62.2, C63.2, C64.2, C65.2, C68.2, C69.2, C70.2, C71.2, C72.2, C73.2, C74.2, C77.2, C78.2, C79.2, C80.2, C81.2, C82.2, C83.2, C86.2, C87.2, C88.2, C89.2, C90.2, C91.2, C92.2, C95.2, C96.2, C97.2, C98.2, C99.2, C100.2, CAN.4, D1.2, DC.2, DCC_SYNC.2, DCC_SYNC.4, DCC_SYNC.8, GND.1, MON.2, MON.7, R4.2, R6.2, R7.2, R12.2, R13.2, R14.2, R15.2, R19.2, R20.2, R21.2, R22.2, R26.2, R27.2, R28.2, R29.2, R33.2, R34.2, R35.2, R36.2, R40.2, R41.2, R42.2, R43.2, R47.2, R48.2, R49.2, R50.2, R54.2, R55.2, R56.2, R57.2, R61.2, R62.2, R63.2, R64.2, STM32.9, SWD.5, TEMP0.4, TEMP0.5, TEMP0.6, TEMP0.7, TEMP0.9, TEMP1.4, TEMP1.5, TEMP1.6, TEMP1.9, U1.6, U1.7, U2.9, U2.15, U2.16, U2.17, U3.2, U4.3, U5.2, U6.9, U6.15, U6.16, U6.17, U7.2, U8.3, U9.2, U10.9, U10.15, U10.16, U10.17, U11.2, U12.3, U13.2, U14.9, U14.15, U14.16, U14.17, U15.2, U16.3, U17.2, U18.9, U18.15, U18.16, U18.17, U19.2, U20.3, U21.2, U22.9, U22.15, U22.16, U22.17, U23.2, U24.3, U25.2, U26.9, U26.15, U26.16, U26.17, U27.2, U28.3, U29.2, U30.9, U30.15, U30.16, U30.17, U31.2, U32.3, U33.2, Y1.2
dc/VPWR: C2.1, C3.1, D1.1, L1.1, MON.10, Q1.5, R1.1, U1.1
hse: HSE.1, STM32.10, Y1.3
link/V5_LINK: C18.1, C19.1, C21.1, CAN.8, DCC_SYNC.16, LNK.2, LNK+.1, LNK_BUCK.3
link/VLINK: C15.1, L2.1, LNK1.1, LNK1.3, LNK2.1, LNK2.3
link/VLINK_GND: C15.2, C16.2, C18.2, C19.2, C21.2, CAN.7, DCC_SYNC.9, DCC_SYNC.15, LNK1.2, LNK1.6, LNK2.2, LNK2.6, LNK-.1, LNK_BUCK.2, R5.2
link/dcc-de: DCC_SYNC.5, R6.1
link/fdcan.rx: CAN.3, STM32.62
link/fdcan.tx: CAN.2, STM32.63
link/jacks/CANH: CAN.6, LNK1.4, LNK2.4
link/jacks/CANL: CAN.5, LNK1.5, LNK2.5
link/jacks/DCC_A: DCC_SYNC.12, LNK1.7, LNK2.7
link/jacks/DCC_B: DCC_SYNC.13, LNK1.8, LNK2.8
nALERT: MON.3, R2.1, STM32.58
nrst: C24.1, STM32.12, SWD.3
swd/swd.swclk: STM32.46, SWD.2
swd/swd.swdio: STM32.45, SWD.1
track/VREF: C11.1, C12.1, R3.2, R4.1, U2.5, U6.5, U10.5, U14.5, U18.5, U22.5, U26.5, U30.5, VREF.1
track/VTRK: C7.1, C8.1, C9.1, C10.1, C29.1, C31.1, C38.1, C40.1, C47.1, C49.1, C56.1, C58.1, C65.1, C67.1, C74.1, C76.1, C83.1, C85.1, C92.1, C94.1, MON.8, MON.9, R1.2, U2.11, U6.11, U10.11, U14.11, U18.11, U22.11, U26.11, U30.11, VTRK.1
track/i2c.scl: MON.5, R9.1, SCL.1, STM32.60, TEMP0.2, TEMP1.2
track/i2c.sda: MON.4, R8.1, SDA.1, STM32.61, TEMP0.1, TEMP1.1
track/logic.rail: 3V3_BUCK.3, C5.2, C6.1, C13.1, C14.1, C17.1, C20.1, C22.1, C23.1, C25.1, C26.1, C27.1, C28.1, C32.1, C35.1, C36.1, C41.1, C44.1, C45.1, C50.1, C53.1, C54.1, C59.1, C62.1, C63.1, C68.1, C71.1, C72.1, C77.1, C80.1, C81.1, C86.1, C89.1, C90.1, C95.1, C98.1, C99.1, CAN.1, DCC_SYNC.1, DCC_SYNC.6, MON.1, MON.6, R2.2, R3.1, R8.2, R9.2, R11.2, R18.2, R25.2, R32.2, R39.2, R46.2, R53.2, R60.2, REG.2, STM32.6, STM32.7, STM32.8, SWD.4, TEMP0.8, TEMP1.7, TEMP1.8, U3.5, U4.5, U5.5, U7.5, U8.5, U9.5, U11.5, U12.5, U13.5, U15.5, U16.5, U17.5, U19.5, U20.5, U21.5, U23.5, U24.5, U25.5, U27.5, U28.5, U29.5, U31.5, U32.5, U33.5, Y1.1, Y1.4
